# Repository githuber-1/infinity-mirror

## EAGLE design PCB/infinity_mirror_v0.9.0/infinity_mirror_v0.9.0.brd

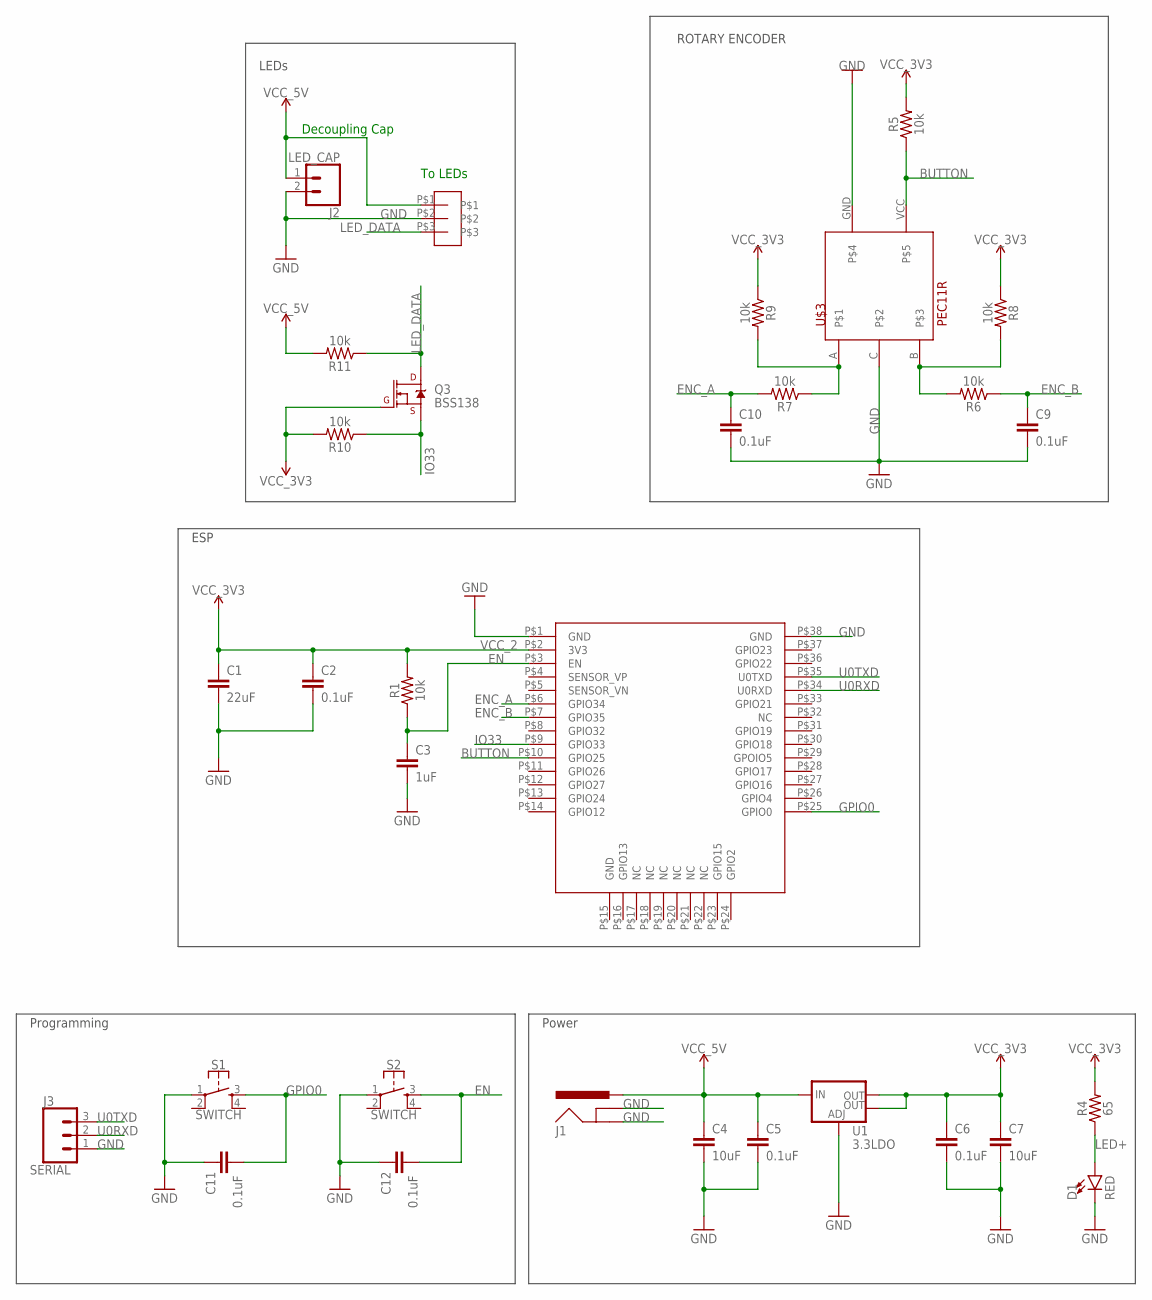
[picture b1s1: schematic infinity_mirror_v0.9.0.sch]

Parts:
C1: 22uF; 0805
C2, C5, C6, C9, C10, C11, C12: 0.1uF; 0805
C3: 1uF; 0805
C4, C7: 10uF; 0805
D1: RED; LED-1206
J1: POWER_JACKPTH_BREAD; POWER_JACK_PTH_BREAD
J2: LED_CAP; 1X02
J3: SERIAL; 1X03
Q3: BSS138; SOT23-3
R1, R5, R6, R7, R8, R9, R10, R11: 10k; 0805
R4: 65; 0805
S1, S2: SWITCH; TACTILE_SWITCH_SMD_5.2MM
U1: 3.3LDO; SOT223
U$1: ESP32-WROOM-32E
U$2: 3-PIN-JST
U$3: PEC11R; PEC11R-4320F-S0012

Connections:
BUTTON: R5.1, U$1.P$10 (GPIO25), U$3.VCC
EN: C3.1, C12.2, R1.1, S2.3, U$1.P$3 (EN)
ENC_A: C10.1, R7.2, U$1.P$6 (GPIO34)
ENC_B: C9.1, R6.1, U$1.P$7 (GPIO35)
GND: C1.2, C2.2, C3.2, C4.2, C5.2, C6.2, C7.2, C9.2, C10.2, C11.1, C12.1, D1.C, J1.GND, J1.GNDBREAK, J2.2, J3.1, S1.1, S2.1, U1.1 (ADJ), U$1.P$1 (GND), U$1.P$38 (GND), U$2.P$2, U$3.C, U$3.GND
GPIO0: C11.2, S1.3, U$1.P$25 (GPIO0)
IO33: Q3.2 (S), R10.1, U$1.P$9 (GPIO33)
LED+: D1.A, R4.1
LED_DATA: Q3.3 (D), R11.1, U$2.P$3
unnamed: R6.2, R8.2, U$3.B
unnamed: R7.1, R9.2, U$3.A
U0RXD: J3.2, U$1.P$34 (U0RXD)
U0TXD: J3.3, U$1.P$35 (U0TXD)
VCC_1: C4.1, C5.1, J1.PWR, J2.1, R11.2, U1.3 (IN), U$2.P$1
VCC_2: C1.1, C2.1, C6.1, C7.1, Q3.1 (G), R1.2, R4.2, R5.2, R8.1, R9.1, R10.2, U1.2 (OUT), U1.4 (OUT), U$1.P$2 (3V3)

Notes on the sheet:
To LEDs
ROTARY ENCODER
Decoupling Cap
Programming
Power
LEDs
ESP

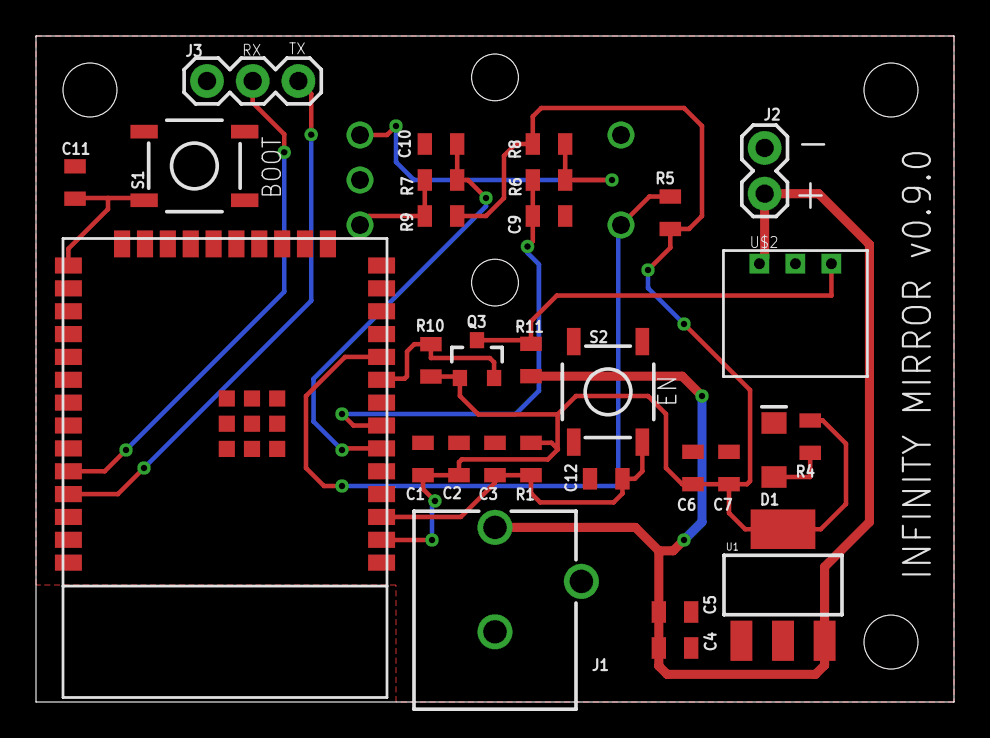
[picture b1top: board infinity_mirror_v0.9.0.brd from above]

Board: 2 copper layers, 51.0 x 37.0 mm, 31 parts (1 on the bottom side), 15 nets.

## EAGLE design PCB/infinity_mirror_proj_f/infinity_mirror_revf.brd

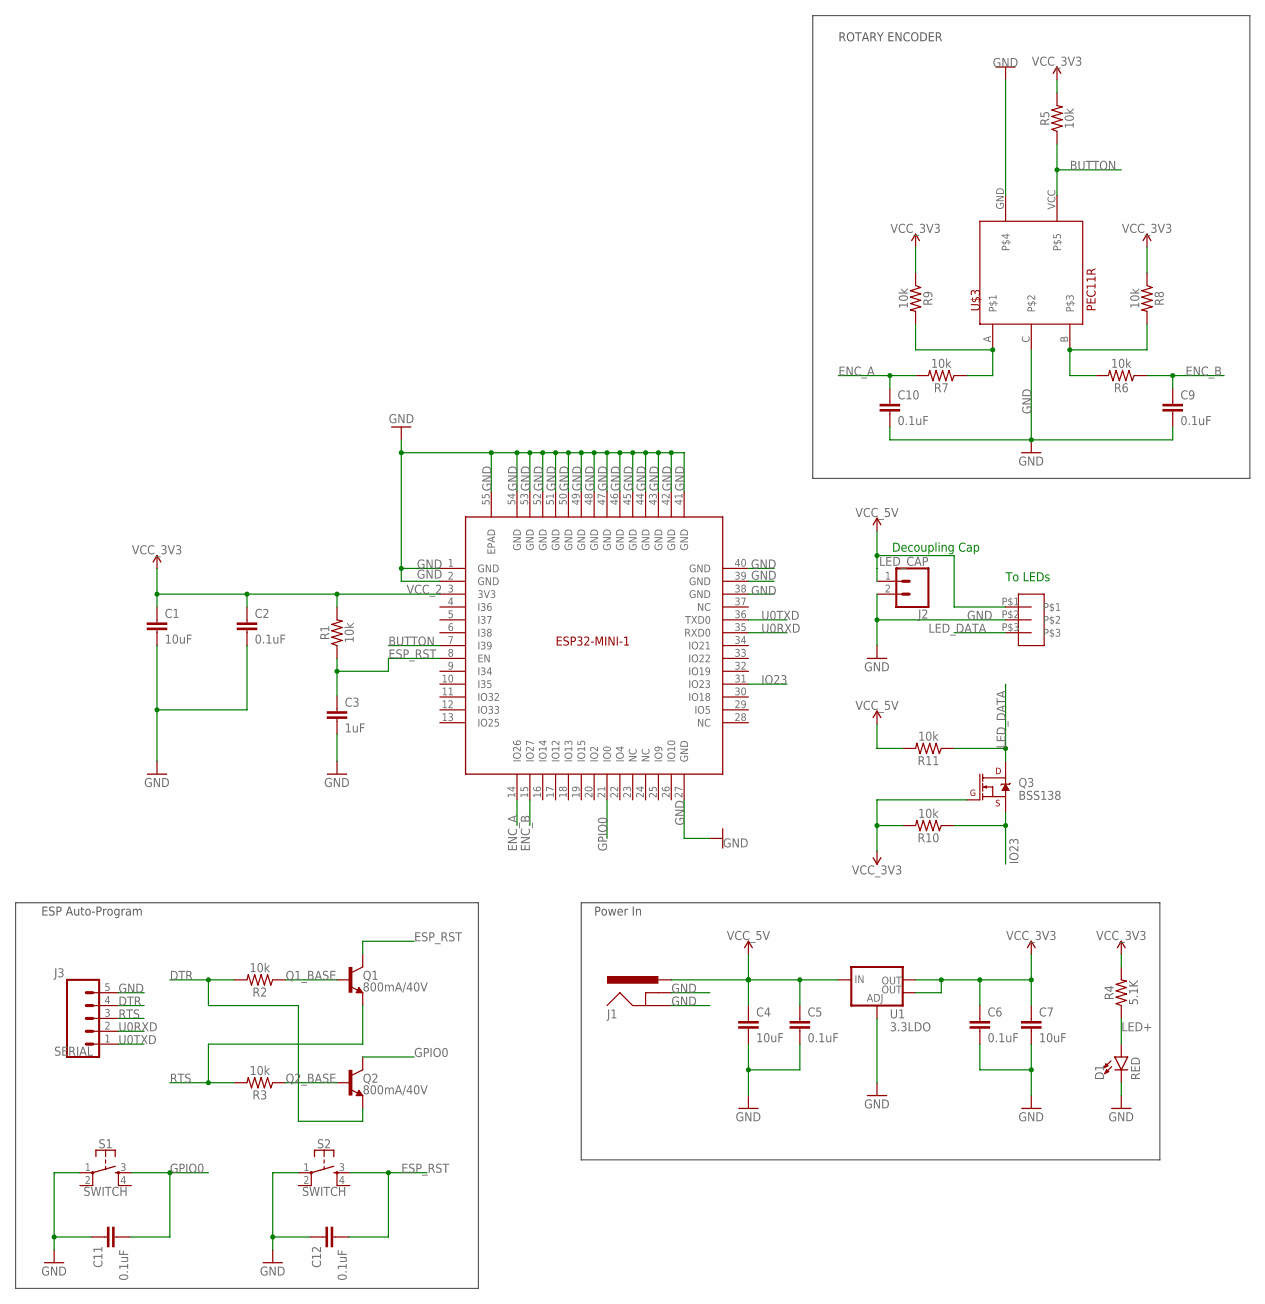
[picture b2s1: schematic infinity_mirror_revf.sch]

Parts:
C1, C4, C7: 10uF; 0805
C2, C5, C6, C9, C10, C11, C12: 0.1uF; 0805
C3: 1uF; 0805
D1: RED; LED-1206
J1: POWER_JACKPTH_BREAD; POWER_JACK_PTH_BREAD
J2: LED_CAP; 1X02
J3: SERIAL; 1X05
Q1, Q2: 800mA/40V; SOT23-3
Q3: BSS138; SOT23-3
R1, R2, R3, R5, R6, R7, R8, R9, R10, R11: 10k; 0805
R4: 5.1K; 0805
S1, S2: SWITCH; TACTILE_SWITCH_SMD_5.2MM
U1: 3.3LDO; SOT223
U$1: ESP32-MINI-1-N4
U$2: 3-PIN-JST
U$3: PEC11R; PEC11R-4320F-S0012

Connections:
BUTTON: R5.1, U$1.7 (I39), U$3.VCC
DTR: J3.4, Q2.2 (E), R2.2
ENC_A: C10.1, R7.2, U$1.14 (IO26)
ENC_B: C9.1, R6.1, U$1.15 (IO27)
ESP_RST: C3.1, C12.2, Q1.3 (C), R1.1, S2.3, U$1.8 (EN)
GND: C1.2, C2.2, C3.2, C4.2, C5.2, C6.2, C7.2, C9.2, C10.2, C11.1, C12.1, D1.C, J1.GND, J1.GNDBREAK, J2.2, J3.5, S1.1, S2.1, U1.1 (ADJ), U$1.1 (GND), U$1.2 (GND), U$1.27 (GND), U$1.38 (GND), U$1.39 (GND), U$1.40 (GND), U$1.41 (GND), U$1.42 (GND), U$1.43 (GND), U$1.44 (GND), U$1.45 (GND), U$1.46 (GND), U$1.47 (GND), U$1.48 (GND), U$1.49 (GND), U$1.50 (GND), U$1.51 (GND), U$1.52 (GND), U$1.53 (GND), U$1.54 (GND), U$1.55 (EPAD), U$2.P$2, U$3.C, U$3.GND
GPIO0: C11.2, Q2.3 (C), S1.3, U$1.21 (IO0)
IO23: Q3.2 (S), R10.1, U$1.31 (IO23)
LED+: D1.A, R4.1
LED_DATA: Q3.3 (D), R11.1, U$2.P$3
unnamed: R6.2, R8.2, U$3.B
unnamed: R7.1, R9.2, U$3.A
Q1_BASE: Q1.1 (B), R2.1
Q2_BASE: Q2.1 (B), R3.1
RTS: J3.3, Q1.2 (E), R3.2
U0RXD: J3.2, U$1.35 (RXD0)
U0TXD: J3.1, U$1.36 (TXD0)
VCC_1: C4.1, C5.1, J1.PWR, J2.1, R11.2, U1.3 (IN), U$2.P$1
VCC_2: C1.1, C2.1, C6.1, C7.1, Q3.1 (G), R1.2, R4.2, R5.2, R8.1, R9.1, R10.2, U1.2 (OUT), U1.4 (OUT), U$1.3 (3V3)

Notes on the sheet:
To LEDs
Power In
ESP Auto-Program
ROTARY ENCODER
Decoupling Cap

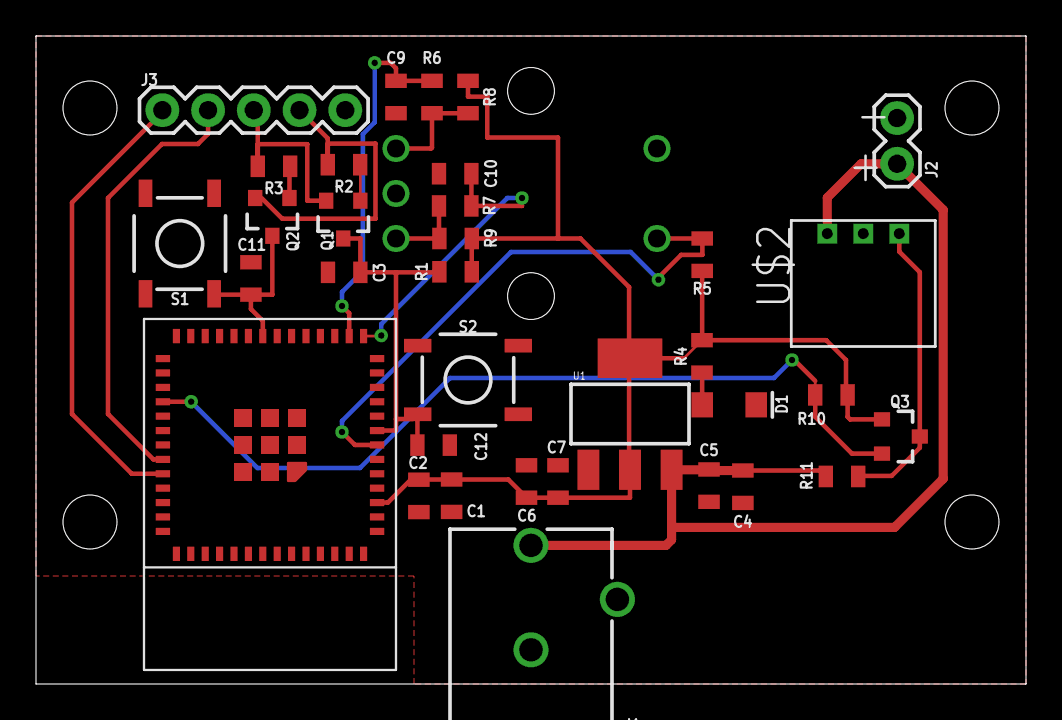
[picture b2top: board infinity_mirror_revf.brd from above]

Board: 2 copper layers, 55.0 x 36.0 mm, 35 parts (1 on the bottom side), 19 nets.

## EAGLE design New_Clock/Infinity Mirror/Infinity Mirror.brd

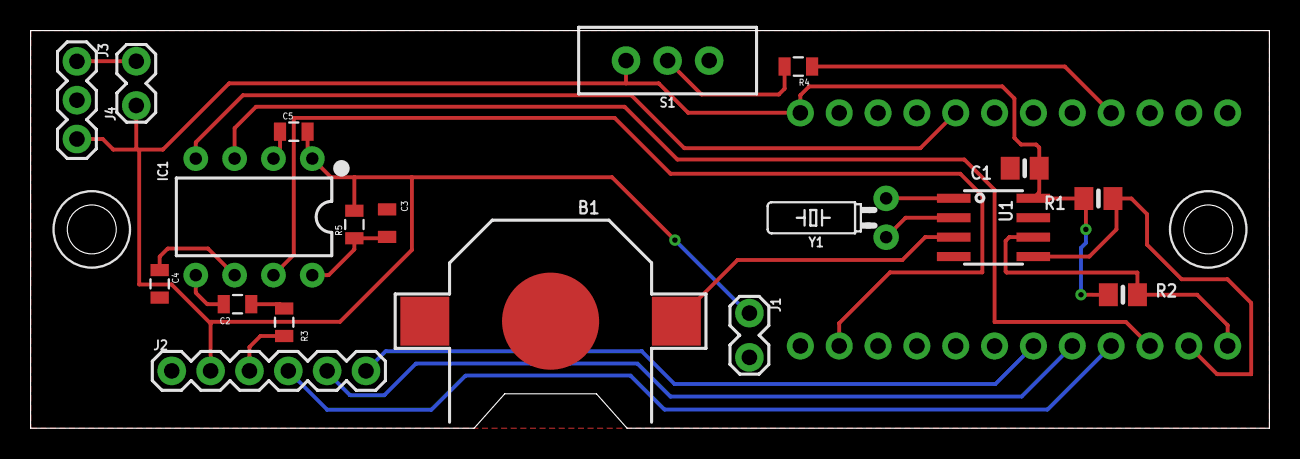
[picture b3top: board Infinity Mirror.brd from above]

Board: 2 copper layers, 81.0 x 26.0 mm, 20 parts (0 on the bottom side), 20 nets.

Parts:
B1: CR1220
C1: 0.1uF; 0805-NO
C2: 0.01uF; SPARKFUN-CAPACITORS_0805
C3: 33pF; 0805
C4, C5: 0.1uF; SPARKFUN-CAPACITORS_0805
IC1: MSGEQ7P; DIP08
J1: Vsupply; SPARKFUN-CONNECTORS_1X02_LOCK
J2: AUDIO_POTS; 1X06
J3: LED; 1X03
J4: LED_CAP; SPARKFUN-CONNECTORS_1X02_LOCK
R1, R2: 10K; 0805-NO
R3: 22k; SPARKFUN-PASSIVES_0805
R4: 220; SPARKFUN-PASSIVES_0805
R5: 200k; SPARKFUN-PASSIVES_0805
S1: SWITCH_SPDT_PTH_11.6X4.0MM_LOCK
U1: DS1307; SOIC8_150MIL
U$1: ADAFRUIT_PRO_TRINKET_NO-DIMENSION; ARDUINO_PRO_TRINKET_5V_NO-DIMENSION
Y1: 32.768kHz; CRYSTAL-PTH-2X6-CYL

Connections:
3: R4.2, S1.2
3-OUT: IC1.3, U$1.TA3
4-STROBE: IC1.4, U$1.T8
6-GND: C4.1, IC1.6
7-RESET: IC1.7, U$1.T~10
8-CKIN: C3.1, IC1.8, R5.1
AUDIO_IN: C2.1, IC1.5
ELECTRET_AUDIO_OUT: J2.3, R3.2
GND: B1.-, C1.2, C3.2, C4.2, C5.1, IC1.2, J1.2, J2.1, J3.1, J4.2, S1.3, U1.4, U$1.TG
unnamed: C2.2, R3.1
POT_1: J2.6, U$1.TA0
POT_2: J2.5, U$1.TA1
POT_3: J2.4, U$1.TA2
SCL: R2.2, U1.6, U$1.TA5
SDA: R1.1, U1.5, U$1.TA4
VBAT: B1.+$1, U1.3
VCC: C1.1, C5.2, IC1.1, J1.1, J2.2, J3.3, J4.1, R1.2, R2.1, R5.2, S1.1, U1.8, U$1.TBAT+
XI: U1.1, Y1.2
XO: U1.2, Y1.1
~3: R4.1, U$1.T~3

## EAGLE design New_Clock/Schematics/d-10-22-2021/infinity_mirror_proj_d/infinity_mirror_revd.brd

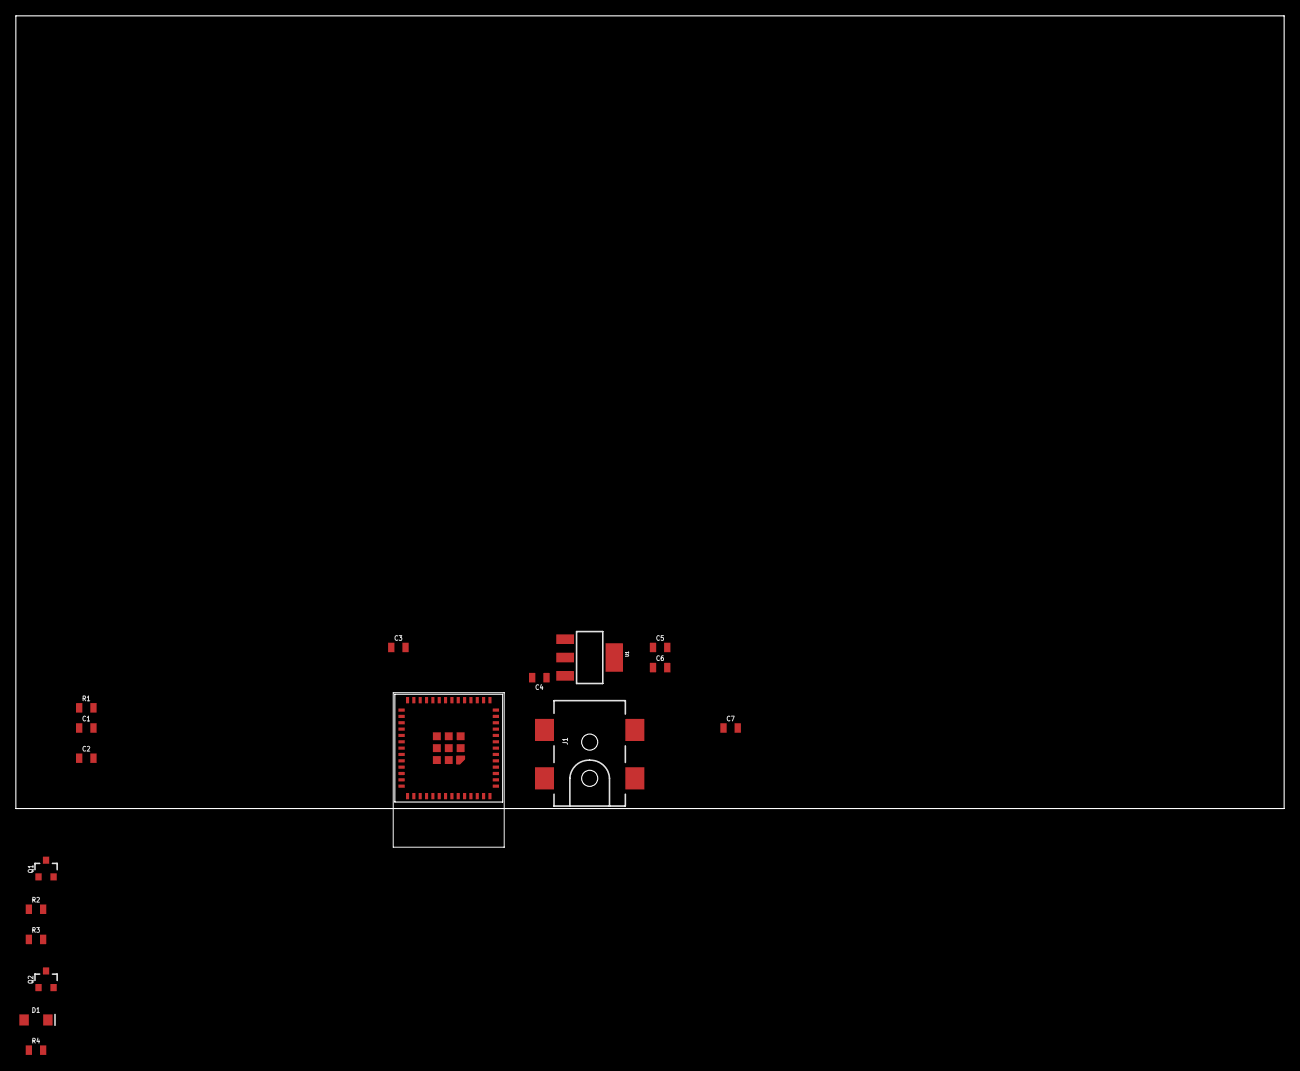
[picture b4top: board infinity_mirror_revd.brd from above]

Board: 2 copper layers, 160.0 x 100.0 mm, 17 parts (0 on the bottom side), 10 nets, no tracks yet.

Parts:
C1, C4, C7: 10uF; 0805
C2, C5, C6: 0.1uF; 0805
C3: 1uF; 0805
D1: RED; LED-1206
J1: 5.5x2.1mm Barrel; POWER_JACK_SMD
Q1, Q2: 800mA/40V; SOT23-3
R1, R2, R3, R4: 10k; 0805
U1: 3.3LDO; SOT223
U$1: ESP32-MINI-1-N4

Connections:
DTR: Q2.2, R2.2
ESP_RST: C3.1, Q1.3, R1.1, U$1.8
GND: C1.2, C2.2, C3.2, C4.2, C5.2, C6.2, C7.2, D1.C, J1.GND, J1.P$4, U1.1, U$1.1, U$1.2, U$1.27, U$1.38, U$1.39, U$1.40, U$1.41, U$1.42, U$1.43, U$1.44, U$1.45, U$1.46, U$1.47, U$1.48, U$1.49, U$1.50, U$1.51, U$1.52, U$1.53, U$1.54, U$1.55
GPIO0: Q2.3, U$1.21
unnamed: Q1.1, R2.1
unnamed: D1.A, R4.1
unnamed: Q2.1, R3.1
RTS: Q1.2, R3.2
VCC_1: C4.1, C5.1, J1.VIN0, U1.3
VCC_2: C1.1, C2.1, C6.1, C7.1, R1.2, R4.2, U1.2, U1.4, U$1.3

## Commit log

2020-05-02 old clock folder
2020-05-02 added trinket and ds1307 to schematic
2020-05-31 board files almost complete
2020-06-02 finished pcb rough draft and BoM
2020-06-02 fixed errors in infinity mirror draft. This one is ordered, hopefully it works :D
2020-06-22 added test code for board-a proving that the clock, 3 analog inputs, daylight-savings time switch and msgeq7 and leds work
2020-06-22 created rec v with a larger board with integrated 8 throw switches. found 3D models and ported circuit box for editing in Fusion. NOTE: THIS CAD IS NOT EXACTLY THE SAME AS THE REAL CLOCK
2021-10-25 esp32 devkit c running 60 leds on esp-idf
2021-11-11 infinity clock base functionality achieved using ESP32-MINI-1
2021-12-13 added power circuitry to revd
2021-12-13 restructured directory for clarity
2021-12-13 added infinity-mirror-sw as submodule
2021-12-20 1st draft schematic and board complete, needs review
2021-12-20 fixed encoder schematic
2021-12-21 added logic level shifting for LEDs and buttons for programming
2022-01-18 fixed airwires and changed programming header from 6 pins to 4 pins
2022-01-19 more airwires. cleaned up silk. changed LED cap to leaded electrolytic
2022-01-21 not sure
2022-01-26 pcb refactor
2022-02-23 encoder footprint fix
2022-11-28 added b and s temp files and chassis
2022-12-08 created rev f and g of PCB and rev b of chassis
2022-12-27 updated infinity mirror sw
2022-12-28 serial connector from 4pin to 3pin. changed led data gpio to reduce trace length
2023-02-15 rev g purchased
2023-02-15 added esp32-wroom32e datasheet
2023-04-03 updated sw submodule
2023-05-05 added chassis files / infinity-mirror-sw updates
2023-05-05 infinity-mirror-sw to latest
2023-05-05 removed ARCHIVE from repo, updated sw peg
2023-05-08 renamed v1.0.0 to v0.9.0, created BoM
2023-05-08 removed pcb backup files
2023-05-08 changed v1.0 to v0.9.0. all chassis files are for printing
2023-07-24 updated pcb directories, sw submodule

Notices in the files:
parts and their libraries:
microbuilder: This work is placed in the public domain, and may be freely used for commercial and non-commercial work with the following conditions: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
SparkFun-IC-Special-Function: Licensing: Creative Commons ShareAlike 4.0 International - https://creativecommons.org/licenses/by-sa/4.0
